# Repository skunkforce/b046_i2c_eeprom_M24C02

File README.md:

# edgy_board number b046
This design is part of the [edgy board project](https://github.com/skunkforce/edgy_boards). It provides the an I2C eeprom. 

# getting started
This repository uses submodules. After cloning use the command 

```$ git submodule update --init --recursive```

to pull the submodules before opening the project with KiCad. 

# Tests
Tests can be found in [TESTS.md](TESTS.md)

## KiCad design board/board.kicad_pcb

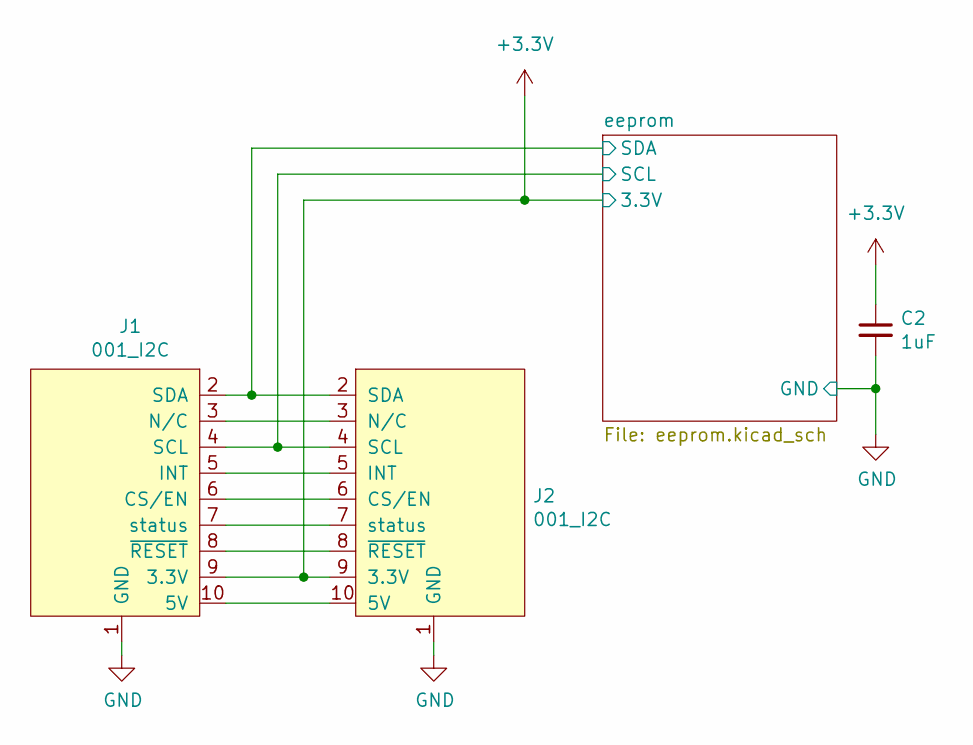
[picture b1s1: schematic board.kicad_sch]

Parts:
C2: 1uF; C_0603_1608Metric; lcsc C15849
J1: 001_I2C; on_edge_2x05_device
J2: 001_I2C; on_edge_2x05_host

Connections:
+3.3V: C2.1, J1.9 (3.3V), J2.9 (3.3V); also elsewhere on the board
/eeprom/SCL: J1.4 (SCL), J2.4 (SCL); also elsewhere on the board
/eeprom/SDA: J1.2 (SDA), J2.2 (SDA); also elsewhere on the board
GND: C2.2, J1.1 (GND), J2.1 (GND); also elsewhere on the board
unnamed: J1.10 (5V), J2.10 (5V)
unnamed: J1.6 (CS/EN), J2.6 (CS/EN)
unnamed: J1.5 (INT), J2.5 (INT)
unnamed: J1.3 (N/C), J2.3 (N/C)
unnamed: J1.7 (status), J2.7 (status)
unnamed: J1.8 (~RESET), J2.8 (~RESET)

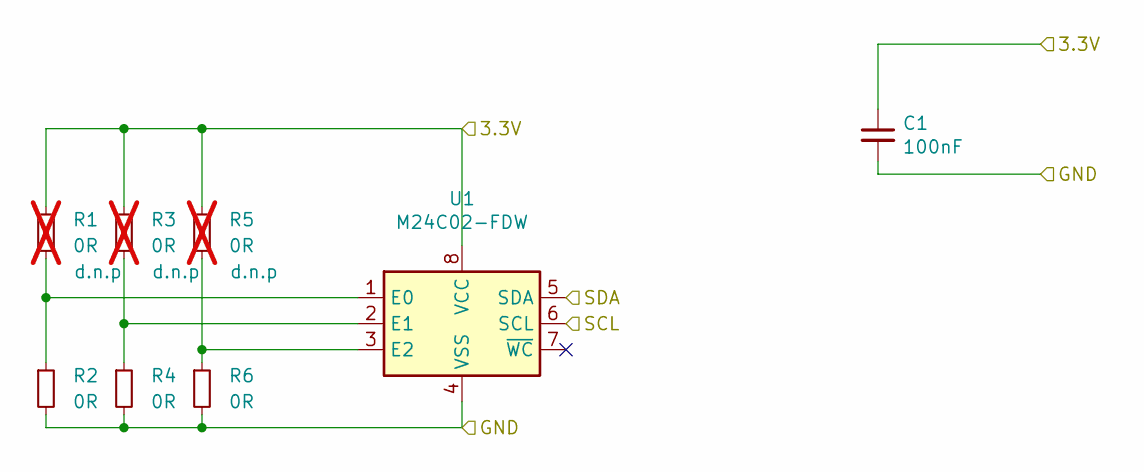
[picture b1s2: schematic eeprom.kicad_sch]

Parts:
C1: 100nF; C_0603_1608Metric; lcsc C14663
R1, R3, R5: 0R; R_0603_1608Metric; lcsc C21189; not fitted
R2, R4, R6: 0R; R_0603_1608Metric; lcsc C21189
U1: M24C02-FDW; TSSOP-8_4.4x3mm_P0.65mm; lcsc C152731

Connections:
+3.3V: C1.1, R1.1, R3.1, R5.1, U1.8 (VCC); also elsewhere on the board
/eeprom/SCL: U1.6 (SCL); also elsewhere on the board
/eeprom/SDA: U1.5 (SDA); also elsewhere on the board
GND: C1.2, R2.2, R4.2, R6.2, U1.4 (VSS); also elsewhere on the board
unnamed: R1.2, R2.1, U1.1 (E0)
unnamed: R3.2, R4.1, U1.2 (E1)
unnamed: R5.2, R6.1, U1.3 (E2)

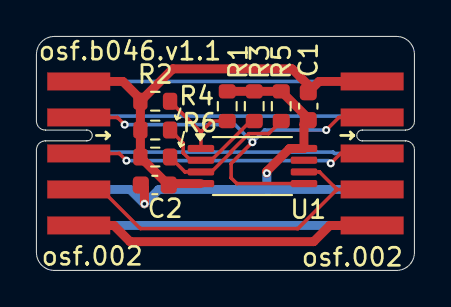
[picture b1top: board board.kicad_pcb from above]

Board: 2 copper layers, 21.0 x 13.0 mm, 11 parts (0 on the bottom side), 13 nets.

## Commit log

2024-07-07 added lcsc numbers and updated to kicad 8
